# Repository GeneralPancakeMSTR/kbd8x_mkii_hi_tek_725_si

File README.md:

# KBD8XMKII "Space Invaders" TKL
PCB For NMB Hi-Tek Series 725 "Space Invaders" Switches and KBDFans KBD8XMKII TKL Keyboard. 

It's for this keyboard:

<center><p>My personal KBD8XMKII Keyboard</p></center>

Probably *literally* that keyboard, which is mine (I can only imagine the Venn diagram of Space Invaders collectors and KBD8XMKII owners is two distant circles). It's a [KBDFans](https://kbdfans.com/) KBD8XMKII, which isn't made anymore. I don't even think you can find it on their website, which seems to just [redirect you to their MKIII](https://kbdfans.com/collections/kbd8x-mkii-1) when you go looking for it. 

Anyway, the [KBD8XMKII](https://ai03.com/projects/kbd8x-mkii/) (scroll to the bottom for the PCB and plate files) was a keyboard designed by the renowned ai03, who graciously open-sourced the project, which helped make this one possible by derivation. Thanks! 

This PCB is specifically designed for use with [NMB Hi-Tek Series 725 "Space Invaders" switches](https://telcontar.net/KBK/Hi-Tek/Series_725) (this is the first link a search came up with), which also aren't made anymore. As you can see, this project has truly reached maximum usefulness. 

<center><p>A Beige (tactile) NMB Hi-Tek Series 725 "Space Invaders" Switch </p></center>

I've been a mechanical keyboard hobbyist for a while now (a decade?), and I've wanted to make my own keyboard about from the beginning. The hangup for me has always been the PCB, so instead of trying to make an expensive CNC case and (hopefully) figuring out the PCB later, I finally decided that to push that particular project forward I would learn the PCB side of things and then revisit the case aspect with some new knowledge and experience under my belt. 

## Reference Photos 
- PCB Top 

- PCB Bottom

- Schematic (Logic)

- Schematic (Matrix)

- Layout/PCB 

- Layout/PCB (MCU + USB)

- Layout/PCB (USB)

- Layout/PCB (MCU)

## Notes 
- If shims are needed, these could be an option: [Clipped Washer 18-8 Stainless Steel, for M2 Screw Size, 2.200 mm ID, 4.500 mm OD](https://www.mcmaster.com/96025A268/)

- **IMPORTANT**: The placement of the Atmega32u4 in JLCPCB's PCBA may be wrong and need to be rotated. If you are getting this PCB made with PCBA, **quadruple check the placement of all of the components.**

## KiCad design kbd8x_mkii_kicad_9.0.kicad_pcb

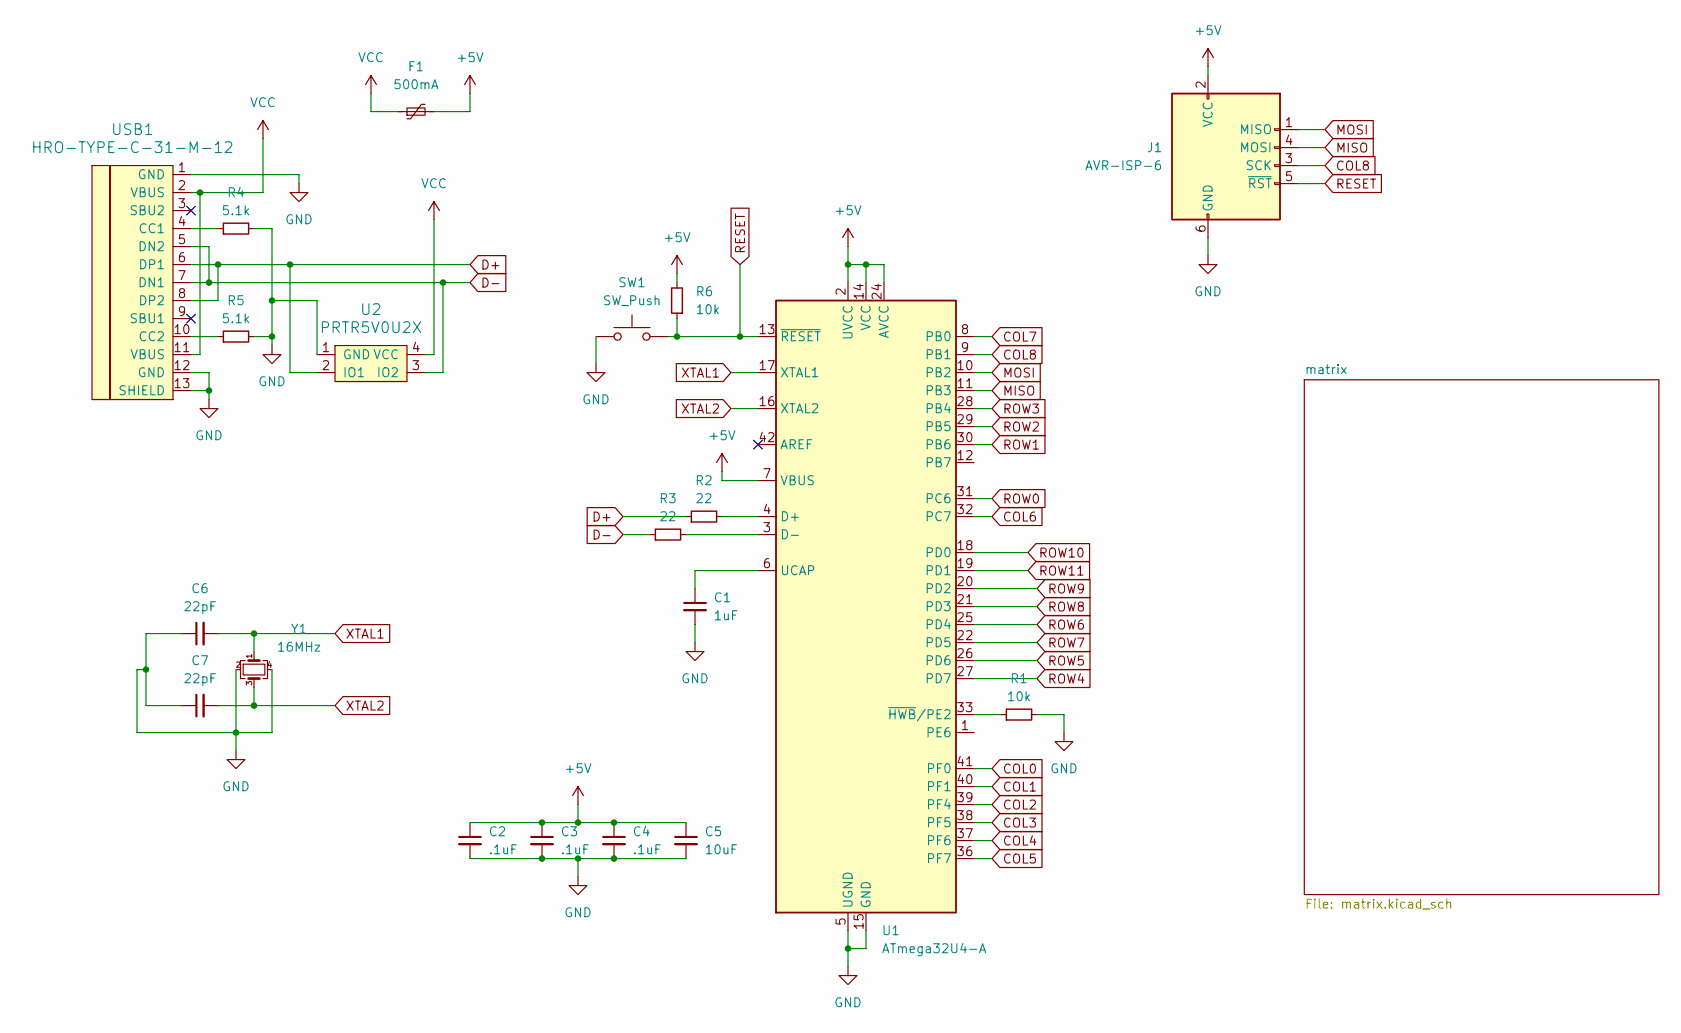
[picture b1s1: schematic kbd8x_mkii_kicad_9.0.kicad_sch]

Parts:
C1: 1uF; C_0805_2012Metric
C2, C3, C4: .1uF; C_0805_2012Metric
C5: 10uF; C_0805_2012Metric
C6, C7: 22pF; C_0805_2012Metric
F1: 500mA; Fuse_1206_3216Metric
J1: AVR-ISP-6; Reset_Pretty-Mask
R1, R6: 10k; R_0805_2012Metric
R2, R3: 22; R_0805_2012Metric
R4, R5: 5.1k; R_0805_2012Metric
SW1: SW_Push; SW_SPST_SKQG_WithStem
U1: ATmega32U4-A; TQFP-44_10x10mm_P0.8mm
U2: PRTR5V0U2X; SOT143B
USB1: HRO-TYPE-C-31-M-12
Y1: 16MHz; Crystal_SMD_3225-4Pin_3.2x2.5mm

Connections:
+5V: C2.1, C3.1, C4.1, C5.1, F1.2, J1.2 (VCC), R6.2, U1.2 (UVCC), U1.7 (VBUS), U1.14 (VCC), U1.24 (AVCC), U1.34 (VCC), U1.44 (AVCC)
COL0: U1.41 (PF0); also elsewhere on the board
COL1: U1.40 (PF1); also elsewhere on the board
COL2: U1.39 (PF4); also elsewhere on the board
COL3: U1.38 (PF5); also elsewhere on the board
COL4: U1.37 (PF6); also elsewhere on the board
COL5: U1.36 (PF7); also elsewhere on the board
COL6: U1.32 (PC7); also elsewhere on the board
COL7: U1.8 (PB0); also elsewhere on the board
COL8: J1.3 (SCK), U1.9 (PB1); also elsewhere on the board
D+: R2.1, U2.2 (IO1), USB1.6 (DP1), USB1.8 (DP2)
D-: R3.1, U2.3 (IO2), USB1.5 (DN2), USB1.7 (DN1)
GND: C1.2, C2.2, C3.2, C4.2, C5.2, C6.1, C7.1, J1.6 (GND), R1.2, R4.2, R5.2, SW1.1, U1.5 (UGND), U1.15 (GND), U1.23 (GND), U1.35 (GND), U1.43 (GND), U2.1 (GND), USB1.1 (GND), USB1.12 (GND), USB1.13 (SHIELD), Y1.2, Y1.4
MISO: J1.4 (MOSI), U1.11 (PB3)
MOSI: J1.1 (MISO), U1.10 (PB2)
unnamed: R2.2, U1.4 (D+)
unnamed: R3.2, U1.3 (D-)
unnamed: C1.1, U1.6 (UCAP)
unnamed: R1.1, U1.33 (~HWB/PE2)
unnamed: R4.1, USB1.4 (CC1)
unnamed: R5.1, USB1.10 (CC2)
RESET: J1.5 (~RST), R6.1, SW1.2, U1.13 (~RESET)
ROW0: U1.31 (PC6); also elsewhere on the board
ROW1: U1.30 (PB6); also elsewhere on the board
ROW2: U1.29 (PB5); also elsewhere on the board
ROW3: U1.28 (PB4); also elsewhere on the board
ROW4: U1.27 (PD7); also elsewhere on the board
ROW5: U1.26 (PD6); also elsewhere on the board
ROW6: U1.25 (PD4); also elsewhere on the board
ROW7: U1.22 (PD5); also elsewhere on the board
ROW8: U1.21 (PD3); also elsewhere on the board
ROW9: U1.20 (PD2); also elsewhere on the board
ROW10: U1.18 (PD0); also elsewhere on the board
ROW11: U1.19 (PD1); also elsewhere on the board
VCC: F1.1, U2.4 (VCC), USB1.2 (VBUS), USB1.11 (VBUS)
XTAL1: C6.2, U1.17 (XTAL1), Y1.1
XTAL2: C7.2, U1.16 (XTAL2), Y1.3

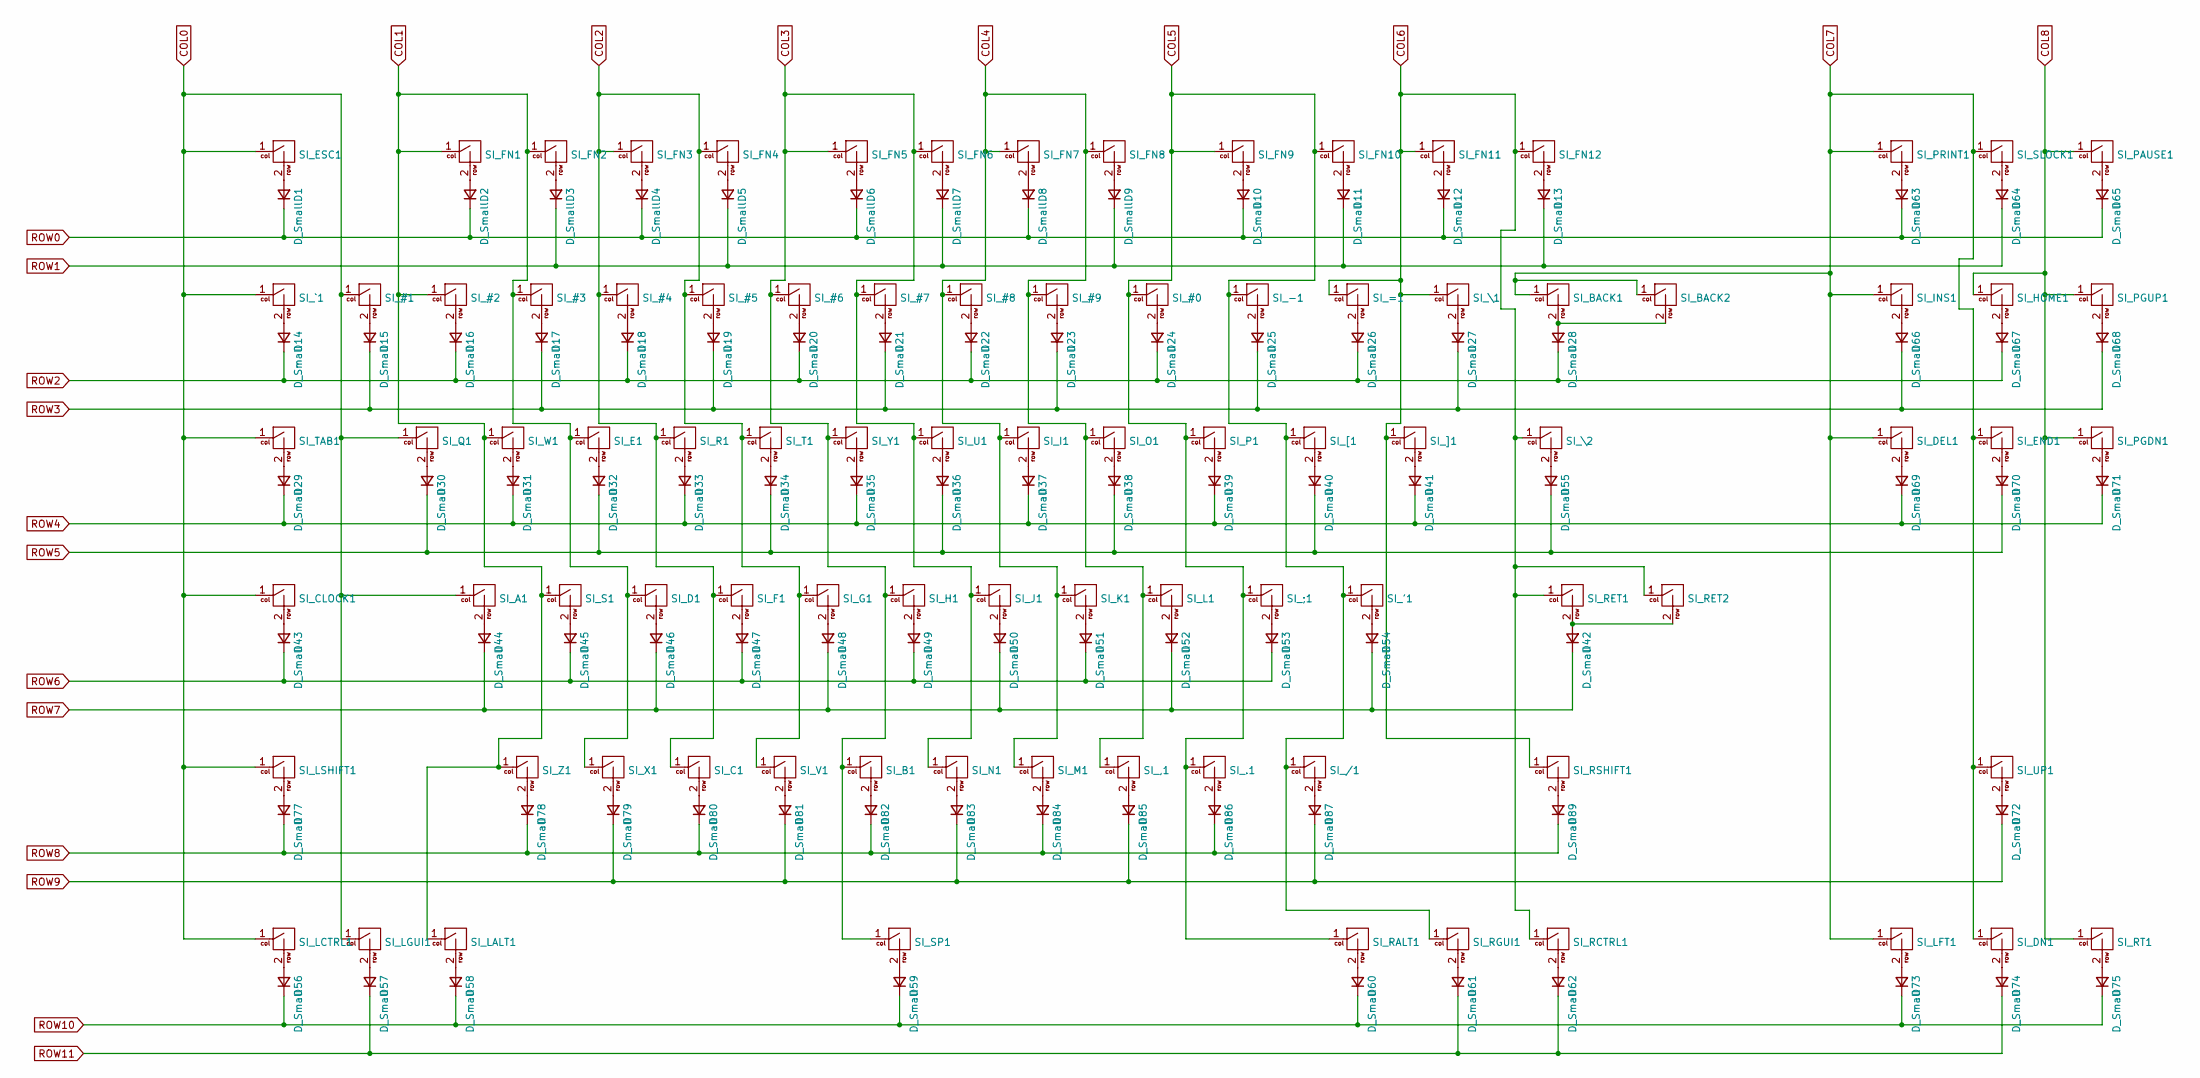
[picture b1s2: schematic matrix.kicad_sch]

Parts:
D1, D2, D3, D4, D5, D6, D7, D8, D9, D10, D11, D12, D13, D14, D15, D16, D17, D18, D19, D20, D21, D22, D23, D24, D25, D26, D27, D28, D29, D30, D31, D32, D33, D34, D35, D36, D37, D38, D39, D40, D41, D42, D43, D44, D45, D46, D47, D48, D49, D50, D51, D52, D53, D54, D55, D56, D57, D58, D59, D60, D61, D62, D63, D64, D65, D66, D67, D68, D69, D70, D71, D72, D73, D74, D75, D77, D78, D79, D80, D81, D82, D83, D84, D85, D86, D87, D89: D_Small; Diode
SI_#0, SI_#1, SI_#2, SI_#3, SI_#4, SI_#5, SI_#6, SI_#7, SI_#8, SI_#9: Hitek725-1U
SI_'1: Hitek725-1U
SI_,1: Hitek725-1U
SI_-1: Hitek725-1U
SI_.1: Hitek725-1U
SI_/1: Hitek725-1U
SI_;1: Hitek725-1U
SI_=1: Hitek725-1U
SI_A1: Hitek725-1U
SI_B1: Hitek725-1U
SI_BACK1, SI_BACK2: Hitek725-1U
SI_C1: Hitek725-1U
SI_CLOCK1: Hitek725-1.75U
SI_D1: Hitek725-1U
SI_DEL1: Hitek725-1U
SI_DN1: Hitek725-1U
SI_E1: Hitek725-1U
SI_END1: Hitek725-1U
SI_ESC1: Hitek725-1U
SI_F1: Hitek725-1U
SI_FN1, SI_FN2, SI_FN3, SI_FN4, SI_FN5, SI_FN6, SI_FN7, SI_FN8, SI_FN9, SI_FN10, SI_FN11, SI_FN12: Hitek725-1U
SI_G1: Hitek725-1U
SI_H1: Hitek725-1U
SI_HOME1: Hitek725-1U
SI_I1: Hitek725-1U
SI_INS1: Hitek725-1U
SI_J1: Hitek725-1U
SI_K1: Hitek725-1U
SI_L1: Hitek725-1U
SI_LALT1: Hitek725-1.5U
SI_LCTRL1: Hitek725-1.5U
SI_LFT1: Hitek725-1U
SI_LGUI1: Hitek725-1U
SI_LSHIFT1: Hitek725-2.25U
SI_M1: Hitek725-1U
SI_N1: Hitek725-1U
SI_O1: Hitek725-1U
SI_P1: Hitek725-1U
SI_PAUSE1: Hitek725-1U
SI_PGDN1: Hitek725-1U
SI_PGUP1: Hitek725-1U
SI_PRINT1: Hitek725-1U
SI_Q1: Hitek725-1U
SI_R1: Hitek725-1U
SI_RALT1: Hitek725-1.5U
SI_RCTRL1: Hitek725-1.5U
SI_RET1: Hitek725-BigAssEnter
SI_RET2: Hitek725-2.25U
SI_RGUI1: Hitek725-1U
SI_RSHIFT1: Hitek725-2.75U
SI_RT1: Hitek725-1U
SI_S1: Hitek725-1U
SI_SLOCK1: Hitek725-1U
SI_SP1: Hitek725-7U
SI_T1: Hitek725-1U
SI_TAB1: Hitek725-1.5U
SI_U1: Hitek725-1U
SI_UP1: Hitek725-1U
SI_V1: Hitek725-1U
SI_W1: Hitek725-1U
SI_X1: Hitek725-1U
SI_Y1: Hitek725-1U
SI_Z1: Hitek725-1U
SI_[1: Hitek725-1U
SI_\1, SI_\2: Hitek725-1U
SI_]1: Hitek725-1U
SI_`1: Hitek725-1U

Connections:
COL0: SI_#1.1, SI_A1.1, SI_CLOCK1.1, SI_ESC1.1, SI_LCTRL1.1, SI_LGUI1.1, SI_LSHIFT1.1, SI_Q1.1, SI_TAB1.1, SI_`1.1; also elsewhere on the board
COL1: SI_#2.1, SI_#3.1, SI_D1.1, SI_E1.1, SI_FN1.1, SI_FN2.1, SI_LALT1.1, SI_S1.1, SI_W1.1, SI_X1.1, SI_Z1.1; also elsewhere on the board
COL2: SI_#4.1, SI_#5.1, SI_C1.1, SI_F1.1, SI_FN3.1, SI_FN4.1, SI_G1.1, SI_R1.1, SI_T1.1, SI_V1.1; also elsewhere on the board
COL3: SI_#6.1, SI_#7.1, SI_B1.1, SI_FN5.1, SI_FN6.1, SI_H1.1, SI_J1.1, SI_N1.1, SI_SP1.1, SI_U1.1, SI_Y1.1; also elsewhere on the board
COL4: SI_#8.1, SI_#9.1, SI_,1.1, SI_FN7.1, SI_FN8.1, SI_I1.1, SI_K1.1, SI_L1.1, SI_M1.1, SI_O1.1; also elsewhere on the board
COL5: SI_#0.1, SI_'1.1, SI_-1.1, SI_.1.1, SI_/1.1, SI_;1.1, SI_FN9.1, SI_FN10.1, SI_P1.1, SI_RALT1.1, SI_RGUI1.1, SI_[1.1; also elsewhere on the board
COL6: SI_=1.1, SI_FN11.1, SI_FN12.1, SI_RCTRL1.1, SI_RET1.1, SI_RET2.1, SI_RSHIFT1.1, SI_\1.1, SI_\2.1, SI_]1.1; also elsewhere on the board
COL7: SI_BACK1.1, SI_BACK2.1, SI_DEL1.1, SI_DN1.1, SI_END1.1, SI_INS1.1, SI_LFT1.1, SI_PRINT1.1, SI_SLOCK1.1, SI_UP1.1; also elsewhere on the board
COL8: SI_HOME1.1, SI_PAUSE1.1, SI_PGDN1.1, SI_PGUP1.1, SI_RT1.1; also elsewhere on the board
unnamed: D1.2 (A), SI_ESC1.2
unnamed: D2.2 (A), SI_FN1.2
unnamed: D3.2 (A), SI_FN2.2
unnamed: D4.2 (A), SI_FN3.2
unnamed: D5.2 (A), SI_FN4.2
unnamed: D6.2 (A), SI_FN5.2
unnamed: D7.2 (A), SI_FN6.2
unnamed: D8.2 (A), SI_FN7.2
unnamed: D9.2 (A), SI_FN8.2
unnamed: D10.2 (A), SI_FN9.2
unnamed: D11.2 (A), SI_FN10.2
unnamed: D12.2 (A), SI_FN11.2
unnamed: D13.2 (A), SI_FN12.2
unnamed: D14.2 (A), SI_`1.2
unnamed: D15.2 (A), SI_#1.2
unnamed: D16.2 (A), SI_#2.2
unnamed: D17.2 (A), SI_#3.2
unnamed: D18.2 (A), SI_#4.2
unnamed: D19.2 (A), SI_#5.2
unnamed: D20.2 (A), SI_#6.2
unnamed: D21.2 (A), SI_#7.2
unnamed: D22.2 (A), SI_#8.2
unnamed: D23.2 (A), SI_#9.2
unnamed: D24.2 (A), SI_#0.2
unnamed: D25.2 (A), SI_-1.2
unnamed: D26.2 (A), SI_=1.2
unnamed: D27.2 (A), SI_\1.2
unnamed: D28.2 (A), SI_BACK1.2, SI_BACK2.2
unnamed: D29.2 (A), SI_TAB1.2
unnamed: D30.2 (A), SI_Q1.2
unnamed: D31.2 (A), SI_W1.2
unnamed: D32.2 (A), SI_E1.2
unnamed: D33.2 (A), SI_R1.2
unnamed: D34.2 (A), SI_T1.2
unnamed: D35.2 (A), SI_Y1.2
unnamed: D36.2 (A), SI_U1.2
unnamed: D37.2 (A), SI_I1.2
unnamed: D38.2 (A), SI_O1.2
unnamed: D39.2 (A), SI_P1.2
unnamed: D40.2 (A), SI_[1.2
unnamed: D41.2 (A), SI_]1.2
unnamed: D42.2 (A), SI_RET1.2, SI_RET2.2
unnamed: D43.2 (A), SI_CLOCK1.2
unnamed: D44.2 (A), SI_A1.2
unnamed: D45.2 (A), SI_S1.2
unnamed: D46.2 (A), SI_D1.2
unnamed: D47.2 (A), SI_F1.2
unnamed: D48.2 (A), SI_G1.2
unnamed: D49.2 (A), SI_H1.2
unnamed: D50.2 (A), SI_J1.2
unnamed: D51.2 (A), SI_K1.2
unnamed: D52.2 (A), SI_L1.2
unnamed: D53.2 (A), SI_;1.2
unnamed: D54.2 (A), SI_'1.2
unnamed: D55.2 (A), SI_\2.2
unnamed: D56.2 (A), SI_LCTRL1.2
unnamed: D57.2 (A), SI_LGUI1.2
unnamed: D58.2 (A), SI_LALT1.2
unnamed: D59.2 (A), SI_SP1.2
unnamed: D60.2 (A), SI_RALT1.2
unnamed: D61.2 (A), SI_RGUI1.2
unnamed: D62.2 (A), SI_RCTRL1.2
unnamed: D63.2 (A), SI_PRINT1.2
unnamed: D64.2 (A), SI_SLOCK1.2
unnamed: D65.2 (A), SI_PAUSE1.2
unnamed: D66.2 (A), SI_INS1.2
unnamed: D67.2 (A), SI_HOME1.2
unnamed: D68.2 (A), SI_PGUP1.2
unnamed: D69.2 (A), SI_DEL1.2
unnamed: D70.2 (A), SI_END1.2
unnamed: D71.2 (A), SI_PGDN1.2
unnamed: D72.2 (A), SI_UP1.2
unnamed: D73.2 (A), SI_LFT1.2
unnamed: D74.2 (A), SI_DN1.2
unnamed: D75.2 (A), SI_RT1.2
unnamed: D77.2 (A), SI_LSHIFT1.2
unnamed: D78.2 (A), SI_Z1.2
unnamed: D79.2 (A), SI_X1.2
unnamed: D80.2 (A), SI_C1.2
unnamed: D81.2 (A), SI_V1.2
unnamed: D82.2 (A), SI_B1.2
unnamed: D83.2 (A), SI_N1.2
unnamed: D84.2 (A), SI_M1.2
unnamed: D85.2 (A), SI_,1.2
unnamed: D86.2 (A), SI_.1.2
unnamed: D87.2 (A), SI_/1.2
unnamed: D89.2 (A), SI_RSHIFT1.2
ROW0: D1.1 (K), D2.1 (K), D4.1 (K), D6.1 (K), D8.1 (K), D10.1 (K), D12.1 (K), D63.1 (K), D65.1 (K); also elsewhere on the board
ROW1: D3.1 (K), D5.1 (K), D7.1 (K), D9.1 (K), D11.1 (K), D13.1 (K), D64.1 (K); also elsewhere on the board
ROW2: D14.1 (K), D16.1 (K), D18.1 (K), D20.1 (K), D22.1 (K), D24.1 (K), D26.1 (K), D28.1 (K), D67.1 (K); also elsewhere on the board
ROW3: D15.1 (K), D17.1 (K), D19.1 (K), D21.1 (K), D23.1 (K), D25.1 (K), D27.1 (K), D66.1 (K), D68.1 (K); also elsewhere on the board
ROW4: D29.1 (K), D31.1 (K), D33.1 (K), D35.1 (K), D37.1 (K), D39.1 (K), D41.1 (K), D69.1 (K), D71.1 (K); also elsewhere on the board
ROW5: D30.1 (K), D32.1 (K), D34.1 (K), D36.1 (K), D38.1 (K), D40.1 (K), D55.1 (K), D70.1 (K); also elsewhere on the board
ROW6: D43.1 (K), D45.1 (K), D47.1 (K), D49.1 (K), D51.1 (K), D53.1 (K); also elsewhere on the board
ROW7: D42.1 (K), D44.1 (K), D46.1 (K), D48.1 (K), D50.1 (K), D52.1 (K), D54.1 (K); also elsewhere on the board
ROW8: D77.1 (K), D78.1 (K), D80.1 (K), D82.1 (K), D84.1 (K), D86.1 (K), D89.1 (K); also elsewhere on the board
ROW9: D72.1 (K), D79.1 (K), D81.1 (K), D83.1 (K), D85.1 (K), D87.1 (K); also elsewhere on the board
ROW10: D56.1 (K), D58.1 (K), D59.1 (K), D60.1 (K), D73.1 (K), D75.1 (K); also elsewhere on the board
ROW11: D57.1 (K), D61.1 (K), D62.1 (K), D74.1 (K); also elsewhere on the board

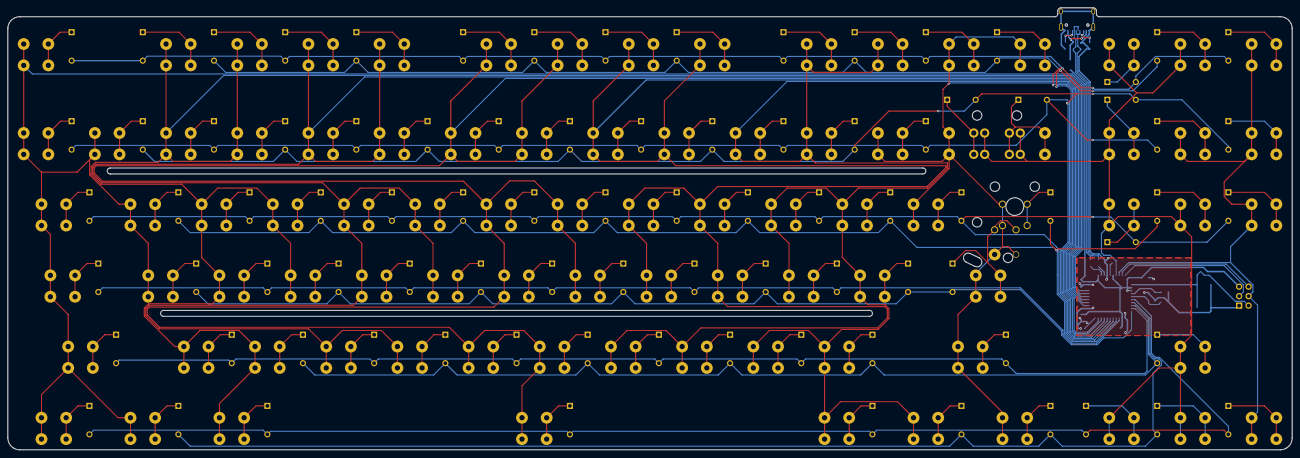
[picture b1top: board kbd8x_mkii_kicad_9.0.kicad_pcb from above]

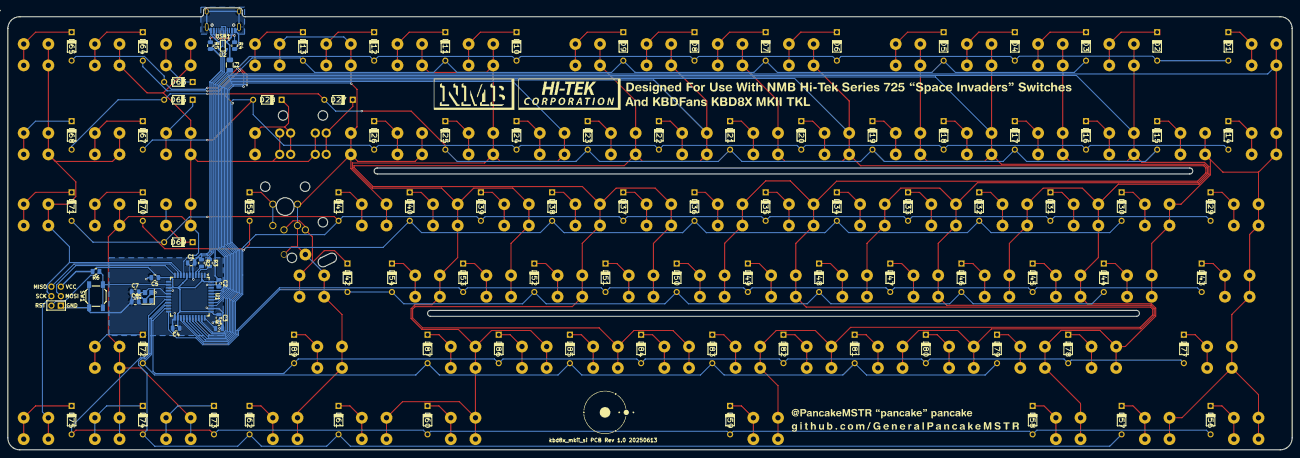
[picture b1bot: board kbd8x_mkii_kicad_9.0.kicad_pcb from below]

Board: 2 copper layers, 343.7 x 118.3 mm, 196 parts (107 on the bottom side), 124 nets.

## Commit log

2025-06-14 Initial Commit.
2025-06-14 Trivial README.
2025-06-15 Light discussion and reference photos (README).
2025-06-20 Revisions to make workable PCB and push before experimenting with some row and column adjustment to attempt to clean up traces.
2025-06-21 Applied row/col on different layers rule to clean up traces, hopefully ready for production.
2025-06-21 Production (Rev 1.0 20250613).
